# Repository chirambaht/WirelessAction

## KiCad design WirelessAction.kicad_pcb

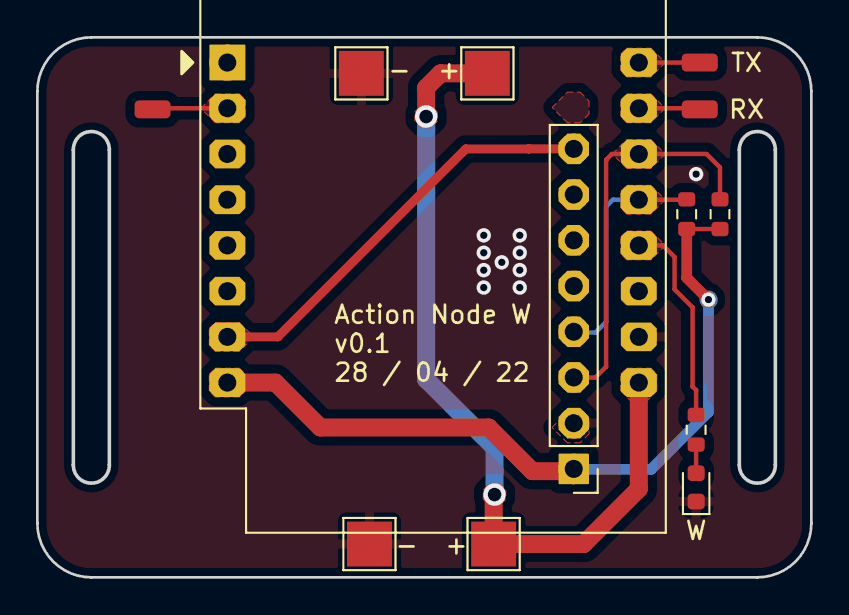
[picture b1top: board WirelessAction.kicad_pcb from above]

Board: 2 copper layers, 43.0 x 29.9 mm, 13 parts (0 on the bottom side), 11 nets.

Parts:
D1: LED; LED_0603_1608Metric
J1: Conn_01x08_Male; PinHeader_1x08_P2.54mm_Vertical
P1: RX; SolderWirePad_1x01_SMD_1x2mm
P2: TX; SolderWirePad_1x01_SMD_1x2mm
P3: SPARE; SolderWirePad_1x01_SMD_1x2mm
P4, P6: -; TestPoint_Pad_2.5x2.5mm
P5, P7: +; TestPoint_Pad_2.5x2.5mm
R1, R2, R3: 10k; R_0603_1608Metric
U1: WeMos_D1_mini; WEMOS_D1_mini_light

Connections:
+3V3: J1.1, R1.1, R2.1, U1.8 (3V3)
/INT: J1.8, U1.7 (CS/D8)
/SCL: J1.3, R2.2, U1.14 (SCL/D1)
/SDA: J1.4, R1.2, U1.13 (SDA/D2)
/WARN: R3.2, U1.12 (D3)
GND: D1.1 (K), J1.2, P4.1, P6.1, U1.10 (GND)
unnamed: D1.2 (A), R3.1
unnamed: P1.1, U1.15 (RX)
unnamed: P2.1, U1.16 (TX)
unnamed: P3.1, U1.2 (A0)
VCC: P5.1, P7.1, U1.9 (5V)

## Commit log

2022-04-28 Ignored
2022-04-28 Some minor changes
